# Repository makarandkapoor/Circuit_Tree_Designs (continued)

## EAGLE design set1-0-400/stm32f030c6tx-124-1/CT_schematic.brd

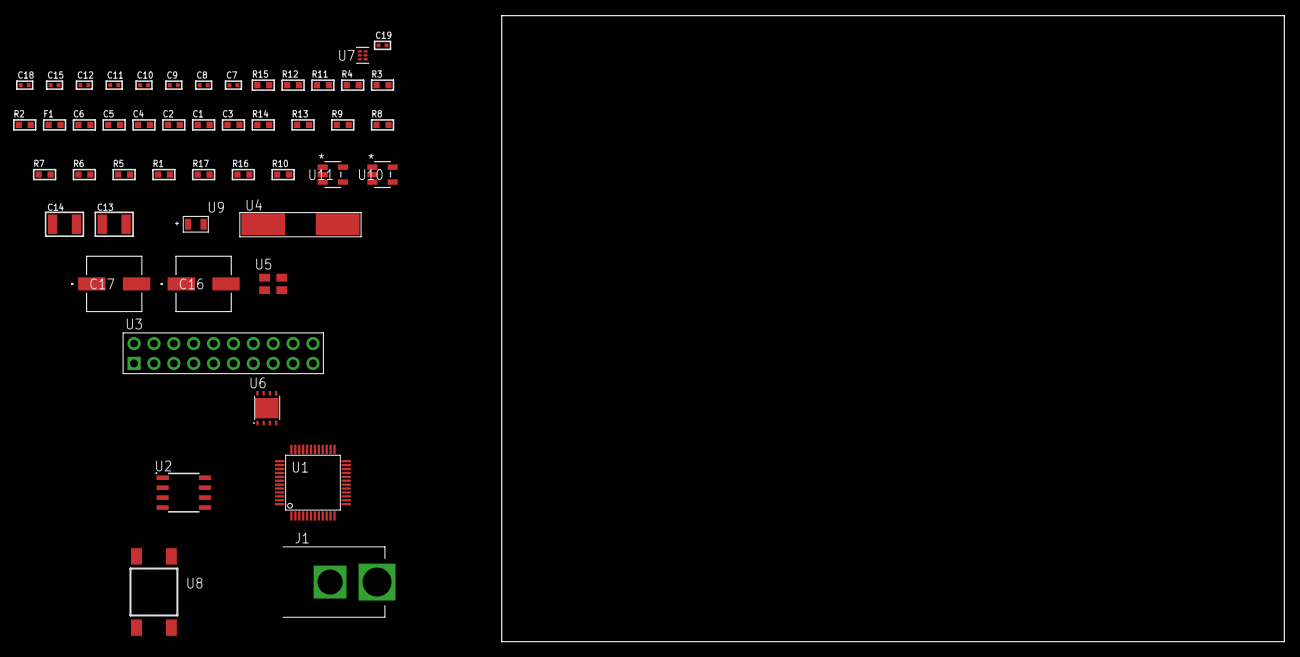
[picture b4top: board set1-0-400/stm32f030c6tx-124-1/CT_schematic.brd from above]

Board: 2 copper layers, 100.0 x 80.0 mm, 49 parts (0 on the bottom side), 27 nets, no tracks yet.

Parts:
C1, C2, C4: 1e-07; C0603
C3: 4.7e-06; C0603
C5: 1e-08; C0603
C6: 1e-06; C0603
C7, C8: 1e-11; C0402
C9, C11, C12, C18, C19: 1e-08; C0402
C10, C15: 1e-07; C0402
C13, C14: 1e-05; C1210
C16, C17: 0.0001; EXV-9H
F1: 240.0; L0603
J1: PJ-037B; PJ-037B_PACKAGE
R1, R5, R6, R7, R8, R9, R13, R14: 10000.0; R0603
R2, R12: 1000.0; R0603
R3: 1600.5; R0603
R4: 4700.0; R0603
R10: 100000.0; R0603
R11: 2231.0; R0603
R15: 9100.0; R0603
R16: 680000.0; R0603
R17: 120000.0; R0603
U1: STM32F030C6T6; LQFP48
U2: AT25040B-SSHL-T; SOIC-8
U3: TST-110-05-T-D-RA
U4: ABLS-25.000MHZ-B2F-T
U5: ASEK-32.768KHz-ECST; ASEK
U6: LP3878SDX-ADJ/NOPB; WSON-8
U7: TPS3895ADRYR; SON-6
U8: 4-1437565-2; SW_4-1437565-2
U9: Q65110A2395; LGM67K-G1J2-24-Z
U10, U11: nc7sz125m5x; NC7SZ125M5X

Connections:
CLK_CRYSTAL_U1_5: C7.1, U1.5, U4.1
CLK_CRYSTAL_U1_6: C8.1, U1.6, U4.2
CLK_U1_3: U1.3, U5.3
GND: C1.2, C2.2, C3.2, C4.2, C5.2, C6.2, C7.2, C8.2, C9.2, C10.2, C11.2, C12.2, C13.2, C14.2, C15.2, C16.2, C17.2, C18.2, C19.2, J1.2, R2.2, R5.2, R12.2, R15.2, R17.2, U1.8, U1.23, U1.47, U2.4, U3.4, U3.6, U3.8, U3.10, U3.12, U3.14, U3.16, U3.18, U3.20, U5.2, U6.3, U6.PAD, U7.2, U9.C, U10.2, U10.3, U11.1, U11.3
NET_U1_7: R4.1, U1.7, U11.4
NET_U1_9: C5.1, C6.1, F1.1, U1.9
NET_U1_44: R5.1, U1.44
NET_U1_45: R3.1, U1.45, U9.A
NET_U1_46: R1.1, U1.46, U8.3, U8.4
NET_U2_3: R6.1, U2.3
NET_U2_7: R8.1, U2.7
NET_U6_1: C12.1, U6.1
NET_U6_6: R11.2, R12.1, U6.6
NET_U6_8: R10.1, U6.8
NET_U7_1: R14.1, R15.1, U7.1
NET_U7_3: R16.2, R17.1, U7.3
NET_U7_4: R13.1, U7.4, U10.4, U11.2
NET_U8_1: R2.1, U8.1, U8.2
PROC_SPI1_MISO: U1.16, U2.2
PROC_SPI1_MOSI: U1.17, U2.5
PROC_SPI1_NSS: R7.1, U1.14, U2.1
PROC_SPI1_SCK: U1.15, U2.6
PROC_SYS_SWCLK: U1.37, U3.9
PROC_SYS_SWDIO: U1.34, U3.7
RST_OUT_U3_SRESET_B: R9.1, U3.15, U10.1
VCC_S1_14V1: C13.1, C16.1, C17.1, J1.1, R10.2, U6.4
VCC_TIER1_3V3: C1.1, C2.1, C3.1, C4.1, C9.1, C10.1, C11.1, C14.1, C15.1, C18.1, C19.1, F1.2, R1.2, R3.2, R4.2, R6.2, R7.2, R8.2, R9.2, R11.1, R13.2, R14.2, R16.1, U1.1, U1.24, U1.48, U2.8, U3.1, U5.4, U6.5, U7.6, U10.5, U11.5

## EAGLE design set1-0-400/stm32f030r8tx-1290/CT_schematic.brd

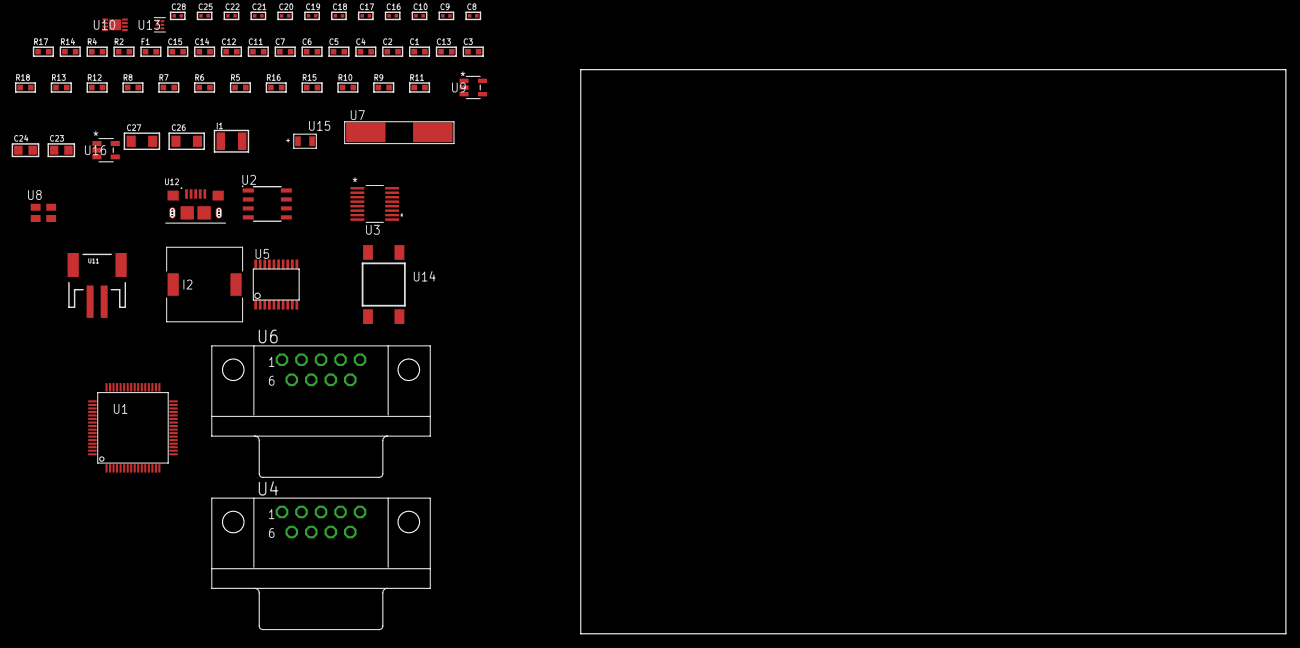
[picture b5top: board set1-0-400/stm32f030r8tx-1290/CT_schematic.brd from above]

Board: 2 copper layers, 63 parts (0 on the bottom side), 53 nets, no tracks yet.

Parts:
C1, C2, C4, C5: 1e-07; C0603
C3: 4.7e-06; C0603
C6: 1e-08; C0603
C7, C11, C12, C14, C15: 1e-06; C0603
C8, C9: 1e-11; C0402
C10, C22, C28: 1e-08; C0402
C13: 2.2e-07; C0603
C16, C17, C18, C19, C20, C21, C25: 1e-07; C0402
C23, C24: 1e-05; C0805
C26, C27: 1e-05; C1206
F1: 240.0; L0603
I1: 1e-05; L1210
I2: 2.5e-06; DR1040
R2: 1000.0; R0603
R4: 4700.0; R0603
R5, R6, R7, R8, R12, R13, R18: 10000.0; R0603
R9: 100000.0; R0603
R10: 220000.0; R0603
R11: 1000000.0; R0603
R14: 9100.0; R0603
R15: 680000.0; R0603
R16: 120000.0; R0603
R17: 2000.0; R0603
U1: STM32F030R8T6; LQFP64
U2: AT25640B-SSHL-T; SOIC-8
U3: LTC2804CGN-1#PBF; SSOP-16
U4, U6: 182-009-113R531; 182-009-MALE
U5: SP3203ECY-L/TR; TSSOP20-I
U7: ABLS-25.000MHZ-B2F-T
U8: ASEK-32.768KHz-ECST; ASEK
U9: ltc3406es5; TSOT-23-5
U10: MCP73831T-2ACI/MC; DFN8_2X3MC
U11: S2B-PH-SM4-TB(LF)(SN); JST-2-SMD
U12: 10118193-0001LF; FCI_10118193-0001LF
U13: TPS3895ADRYR; SON-6
U14: 4-1437565-2; SW_4-1437565-2
U15: Q65110A2395; LGM67K-G1J2-24-Z
U16: nc7sz125m5x; NC7SZ125M5X

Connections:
CLK_CRYSTAL_U1_5: C8.1, U1.5, U7.1
CLK_CRYSTAL_U1_6: C9.1, U1.6, U7.2
CLK_U1_3: U1.3, U8.3
GND: C1.2, C2.2, C3.2, C4.2, C5.2, C6.2, C7.2, C8.2, C9.2, C10.2, C11.2, C12.2, C14.2, C15.2, C16.2, C17.2, C20.2, C21.2, C22.2, C23.2, C24.1, C24.2, C25.2, C26.2, C27.2, C28.2, R2.2, R5.2, R10.2, R14.2, R16.2, R17.2, U1.12, U1.31, U1.63, U2.4, U3.8, U4.5, U5.18, U6.5, U8.2, U9.2, U10.6, U10.9, U11.2, U12.5, U12.6, U12.7, U12.8, U12.9, U13.2, U15.C, U16.1, U16.3
INPUT_USBPOWER_5V: C26.1, R18.2, U10.1, U10.2, U12.1
NET_U1_7: R4.1, U1.7, U16.4
NET_U1_13: C6.1, C7.1, F1.1, U1.13
NET_U1_60: R5.1, U1.60
NET_U1_62: U14.3, U14.4
NET_U2_3: R6.1, U2.3
NET_U2_7: R8.1, U2.7
NET_U3_6: C11.1, U3.6
NET_U3_7: C13.1, I1.2, U3.7
NET_U3_9: C12.1, U3.9
NET_U3_10: C13.2, U3.10
NET_U3_11: R9.1, U3.11
NET_U4_2: U3.1, U4.2
NET_U4_3: U3.3, U4.3
NET_U4_7: U3.2, U4.7
NET_U4_8: U3.4, U4.8
NET_U5_1: C18.1, U5.1
NET_U5_2: C20.1, U5.2
NET_U5_3: C18.2, U5.3
NET_U5_4: C19.1, U5.4
NET_U5_5: C19.2, U5.5
NET_U5_6: C21.1, U5.6
NET_U6_2: U5.14, U6.2
NET_U6_3: U5.17, U6.3
NET_U6_7: U5.13, U6.7
NET_U6_8: U5.16, U6.8
NET_U9_3: I2.1, U9.3
NET_U9_5: R10.1, R11.1, U9.5
NET_U9_ATNET_3: I2.2, R11.2
NET_U10_5: R18.1, U10.5
NET_U10_8: R17.1, U10.8
NET_U13_1: R13.1, R14.1, U13.1
NET_U13_3: R15.2, R16.1, U13.3
NET_U13_4: R12.1, U13.4, U16.2
NET_U14_1: R2.1, U14.1, U14.2
PROC_SPI1_MISO: U1.22, U2.2
PROC_SPI1_MOSI: U1.23, U2.5
PROC_SPI1_NSS: R7.1, U1.20, U2.1
PROC_SPI1_SCK: U1.21, U2.6
PROC_USART1_CTS: U1.44, U5.8
PROC_USART1_RTS: U1.45, U5.10
PROC_USART1_RX: U1.43, U5.11
PROC_USART1_TX: U1.42, U5.7
PROC_USART2_CTS: U1.14, U3.13
PROC_USART2_RTS: U1.15, U3.15
PROC_USART2_RX: U1.17, U3.16
PROC_USART2_TX: U1.16, U3.14
VCC_S1_3V7: C23.1, C27.1, U9.4, U10.3, U10.4, U11.1
VCC_TIER1_3V3: C1.1, C2.1, C3.1, C4.1, C5.1, C10.1, C14.1, C15.1, C16.1, C17.1, C22.1, C24.2, C25.1, C28.1, F1.2, I1.1, I2.2, R4.2, R6.2, R7.2, R8.2, R9.2, R11.2, R12.2, R13.2, R15.1, U1.1, U1.32, U1.64, U2.8, U3.5, U3.12, U5.12, U5.19, U8.4, U13.6, U16.5

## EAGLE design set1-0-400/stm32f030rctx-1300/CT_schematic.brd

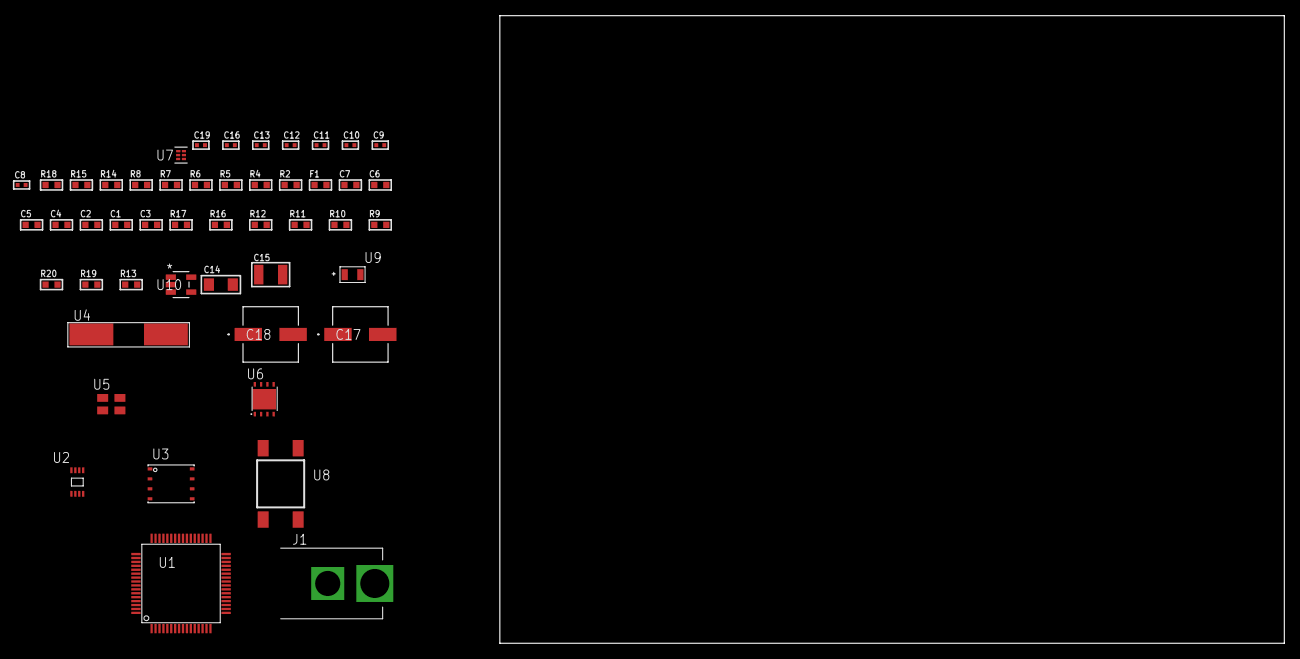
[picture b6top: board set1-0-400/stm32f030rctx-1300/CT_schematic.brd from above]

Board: 2 copper layers, 100.0 x 80.0 mm, 49 parts (0 on the bottom side), 24 nets, no tracks yet.

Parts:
C1, C2, C4, C5: 1e-07; C0603
C3: 4.7e-06; C0603
C6: 1e-08; C0603
C7: 1e-06; C0603
C8, C9: 1e-11; C0402
C10, C11, C12, C13, C19: 1e-08; C0402
C14: 1e-05; C1206
C15: 1e-05; C1210
C16: 1e-07; C0402
C17, C18: 0.0001; EXV-9H
F1: 240.0; L0603
J1: PJ-037B; PJ-037B_PACKAGE
R2, R15: 1000.0; R0603
R4: 4700.0; R0603
R5, R6, R7, R8: 2200.0; R0603
R9, R10, R11, R12, R16, R17: 10000.0; R0603
R13: 100000.0; R0603
R14: 2231.0; R0603
R18: 9100.0; R0603
R19: 680000.0; R0603
R20: 120000.0; R0603
U1: STM32F030RCT6; LQFP64
U2: 24AA04-I/MC; TDFN-8/6MM
U3: 24AA512-I/MF; DFN8-S
U4: ABLS-25.000MHZ-B2F-T
U5: ASEK-32.768KHz-ECST; ASEK
U6: LP3878SDX-ADJ/NOPB; WSON-8
U7: TPS3895ADRYR; SON-6
U8: 4-1437565-2; SW_4-1437565-2
U9: Q65110A2395; LGM67K-G1J2-24-Z
U10: nc7sz125m5x; NC7SZ125M5X

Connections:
CLK_CRYSTAL_U1_5: C8.1, U1.5, U4.1
CLK_CRYSTAL_U1_6: C9.1, U1.6, U4.2
CLK_U1_3: U1.3, U5.3
GND: C1.2, C2.2, C3.2, C4.2, C5.2, C6.2, C7.2, C8.2, C9.2, C10.2, C11.2, C12.2, C13.2, C14.2, C15.2, C16.2, C17.2, C18.2, C19.2, J1.2, R2.2, R9.2, R12.2, R15.2, R18.2, R20.2, U1.12, U1.18, U1.31, U1.47, U1.63, U2.4, U3.4, U5.2, U6.3, U6.PAD, U7.2, U9.C, U10.1, U10.3
NET_U1_7: R4.1, U1.7, U10.4
NET_U1_13: C6.1, C7.1, F1.1, U1.13
NET_U1_29: R7.1, U1.29, U2.6
NET_U1_30: R8.1, U1.30, U2.5
NET_U1_42: R5.1, U1.42, U3.6
NET_U1_43: R6.1, U1.43, U3.5
NET_U1_60: R9.1, U1.60
NET_U1_62: U8.3, U8.4
NET_U3_1: R10.1, U3.1
NET_U3_2: R11.1, U3.2
NET_U3_3: R12.1, U3.3
NET_U6_1: C13.1, U6.1
NET_U6_6: R14.2, R15.1, U6.6
NET_U6_8: R13.1, U6.8
NET_U7_1: R17.1, R18.1, U7.1
NET_U7_3: R19.2, R20.1, U7.3
NET_U7_4: R16.1, U7.4, U10.2
NET_U8_1: R2.1, U8.1, U8.2
VCC_S1_10V2: C14.1, C17.1, C18.1, J1.1, R13.2, U6.4
VCC_TIER1_3V3: C1.1, C2.1, C3.1, C4.1, C5.1, C10.1, C11.1, C12.1, C15.1, C16.1, C19.1, F1.2, R4.2, R5.2, R6.2, R7.2, R8.2, R10.2, R11.2, R14.1, R16.2, R17.2, R19.1, U1.1, U1.19, U1.32, U1.48, U1.64, U2.7, U2.8, U3.7, U3.8, U5.4, U6.5, U7.6, U10.5

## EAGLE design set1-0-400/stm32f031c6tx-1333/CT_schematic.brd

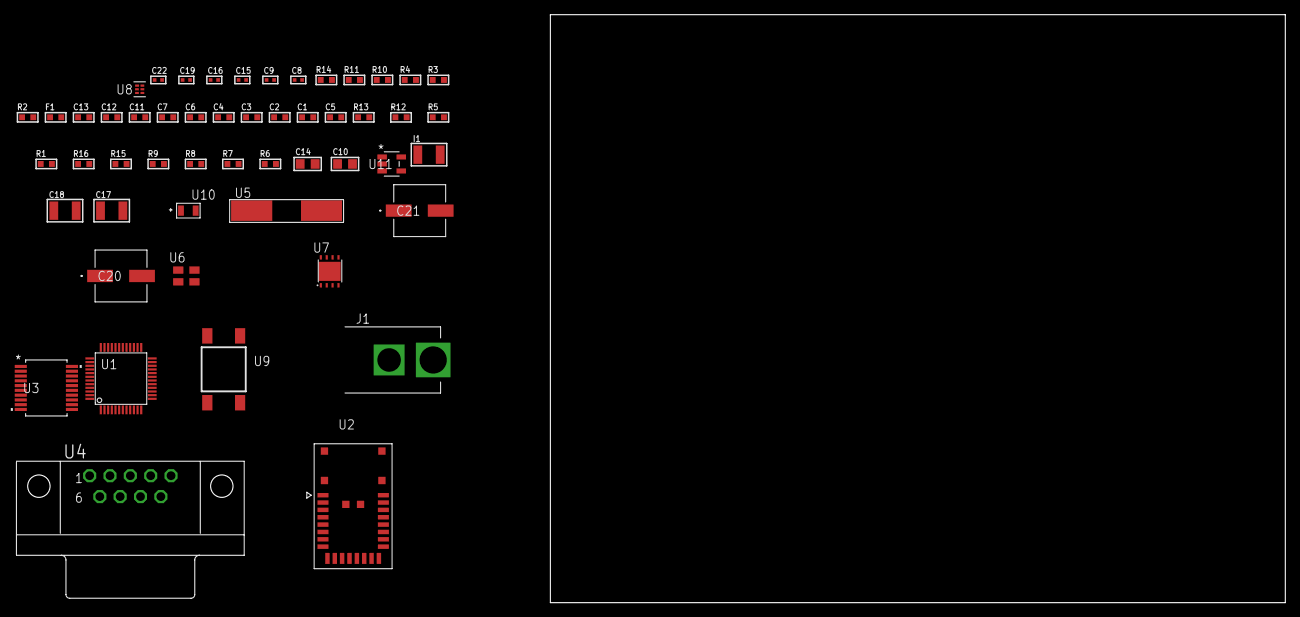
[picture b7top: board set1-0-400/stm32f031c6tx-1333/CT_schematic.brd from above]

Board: 2 copper layers, 100.0 x 80.0 mm, 52 parts (0 on the bottom side), 38 nets, no tracks yet.

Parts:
C1, C7, C11, C12, C13: 1e-06; C0603
C2, C3, C4: 1e-07; C0603
C5: 4.7e-06; C0603
C6: 1e-08; C0603
C8, C9: 1e-11; C0402
C10: 1e-05; C0805
C14: 4.7e-06; C0805
C15, C16, C22: 1e-08; C0402
C17, C18: 1e-05; C1210
C19: 1e-07; C0402
C20, C21: 0.0001; EXV-9H
F1: 240.0; L0603
I1: 1.5e-05; L1210
J1: PJ-037B; PJ-037B_PACKAGE
R1, R5, R12, R13: 10000.0; R0603
R2, R11: 1000.0; R0603
R3: 1600.5; R0603
R4: 4700.0; R0603
R6, R7, R8, R9: 100000.0; R0603
R10: 2231.0; R0603
R14: 9100.0; R0603
R15: 680000.0; R0603
R16: 120000.0; R0603
U1: stm32f031c6t6; LQFP48
U2: A2500R24A00GM
U3: MAX3218EAP+T; SSOP-20
U4: 182-009-113R531; 182-009-MALE
U5: ABLS-25.000MHZ-B2F-T
U6: ASEK-32.768KHz-ECST; ASEK
U7: LP3878SDX-ADJ/NOPB; WSON-8
U8: TPS3895ADRYR; SON-6
U9: 4-1437565-2; SW_4-1437565-2
U10: Q65110A2395; LGM67K-G1J2-24-Z
U11: nc7sz125m5x; NC7SZ125M5X

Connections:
CLK_CRYSTAL_U1_5: C8.1, U1.5, U5.1
CLK_CRYSTAL_U1_6: C9.1, U1.6, U5.2
CLK_U1_3: U1.3, U6.3
GND: C1.2, C2.2, C3.2, C4.2, C5.2, C6.2, C7.2, C8.2, C9.2, C10.2, C11.2, C12.2, C13.2, C15.2, C16.2, C17.2, C18.2, C19.2, C20.2, C21.2, C22.2, J1.2, R2.2, R5.2, R11.2, R14.2, R16.2, U1.8, U1.23, U1.47, U2.8, U2.17, U3.5, U3.17, U3.20, U4.5, U6.2, U7.3, U7.PAD, U8.2, U10.C, U11.1, U11.3
NET_U1_7: R4.1, U1.7, U11.4
NET_U1_9: C6.1, C7.1, F1.1, U1.9
NET_U1_44: R5.1, U1.44
NET_U1_45: R3.1, U1.45, U10.A
NET_U1_46: R1.1, U1.46, U9.3, U9.4
NET_U3_1: I1.1, U3.1
NET_U3_2: R6.1, U3.2
NET_U3_3: R7.1, U3.3
NET_U3_4: R8.1, U3.4
NET_U3_15: C13.1, U3.15
NET_U3_16: C14.2, U3.16
NET_U3_18: C14.1, U3.18
NET_U3_19: C12.1, U3.19
NET_U4_2: U3.12, U4.2
NET_U4_3: U3.14, U4.3
NET_U4_7: U3.11, U4.7
NET_U4_8: U3.13, U4.8
NET_U7_1: C16.1, U7.1
NET_U7_6: R10.2, R11.1, U7.6
NET_U7_8: R9.1, U7.8
NET_U8_1: R13.1, R14.1, U8.1
NET_U8_3: R15.2, R16.1, U8.3
NET_U8_4: R12.1, U8.4, U11.2
NET_U9_1: R2.1, U9.1, U9.2
PROC_SPI1_MISO: U1.16, U2.10
PROC_SPI1_MOSI: U1.17, U2.11
PROC_SPI1_NSS: U1.14, U2.12
PROC_SPI1_SCK: U1.15, U2.9
PROC_USART1_CTS: U1.10, U3.8
PROC_USART1_RTS: U1.11, U3.10
PROC_USART1_RX: U1.13, U3.9
PROC_USART1_TX: U1.12, U3.7
VCC_S1_13V5: C17.1, C20.1, C21.1, J1.1, R9.2, U7.4
VCC_TIER1_3V3: C1.1, C2.1, C3.1, C4.1, C5.1, C10.1, C11.1, C15.1, C18.1, C19.1, C22.1, F1.2, I1.2, R1.2, R3.2, R4.2, R6.2, R7.2, R8.2, R10.1, R12.2, R13.2, R15.1, U1.1, U1.24, U1.48, U2.18, U3.6, U6.4, U7.5, U8.6, U11.5

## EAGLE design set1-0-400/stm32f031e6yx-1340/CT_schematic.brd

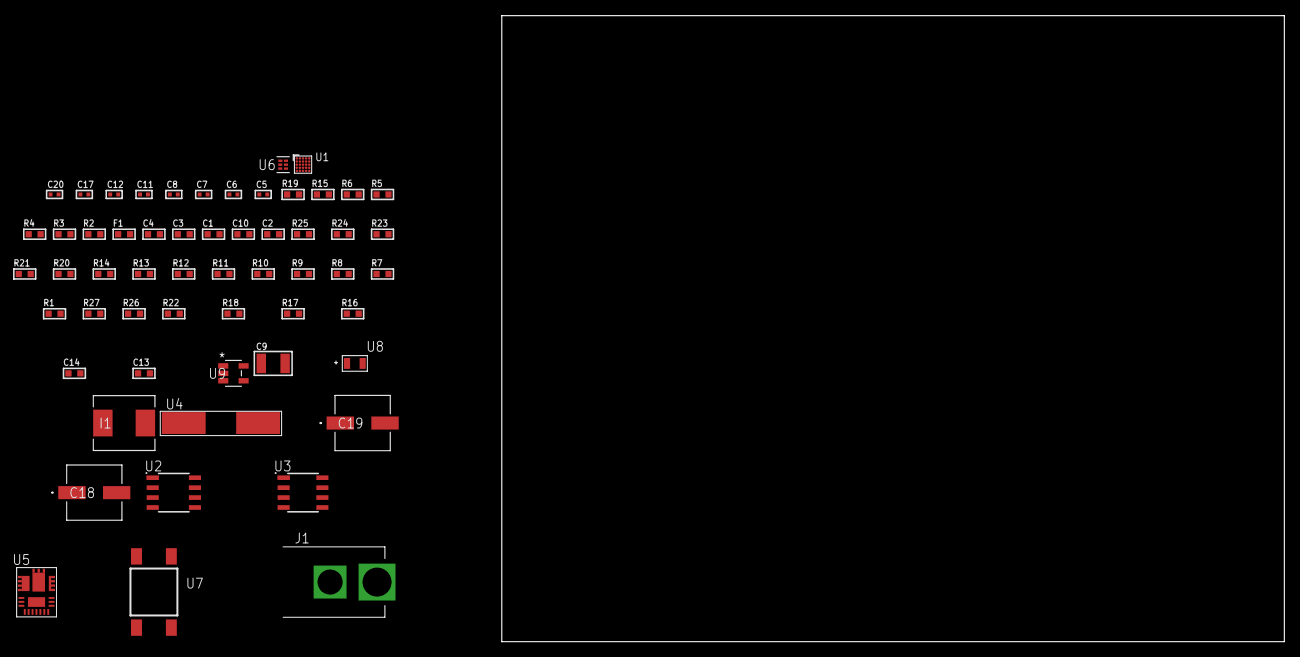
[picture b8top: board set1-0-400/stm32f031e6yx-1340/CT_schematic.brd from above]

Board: 2 copper layers, 100.0 x 80.0 mm, 57 parts (0 on the bottom side), 36 nets, no tracks yet.

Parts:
C1: 1e-07; C0603
C2: 4.7e-06; C0603
C3: 1e-08; C0603
C4: 1e-06; C0603
C5, C6: 1e-11; C0402
C7, C8, C20: 1e-08; C0402
C9: 0.0001; C1210
C10: 2.2e-06; C0603
C11, C12, C17: 1e-07; C0402
C13: 8.5935703950126e-09; R0603
C14: 2.929626271027e-07; R0603
C18, C19: 0.0001; EXV-9H
F1: 240.0; L0603
I1: 6.8e-07; IND25X25CZ
J1: PJ-037B; PJ-037B_PACKAGE
R1, R7, R8, R9, R10, R11, R12, R13, R14, R23, R24: 10000.0; R0603
R2: 1000.0; R0603
R3: 1270.0; R0603
R4: 4700.0; R0603
R5, R6: 2200.0; R0603
R15: 0.1; R0603
R16: 4030.2416170974; R0603
R17: 1007.5604042744; R0603
R18: 59.319518072289; R0603
R19: 130.0; R0603
R20: 39000.0; R0603
R21: 49900.0; R0603
R22: 5216.2133333333; R0603
R25: 18000.0; R0603
R26: 470000.0; R0603
R27: 120000.0; R0603
U1: stm32f031e6y7; WLCSP25
U2: AT25040B-SSHL-T; SOIC-8
U3: AT24C02D-SSHM-T; AT24C02D
U4: ABLS-25.000MHZ-B2F-T
U5: IR3899MTR1PBF
U6: TPS3895ADRYR; SON-6
U7: 4-1437565-2; SW_4-1437565-2
U8: Q65110A2395; LGM67K-G1J2-24-Z
U9: nc7sz125m5x; NC7SZ125M5X

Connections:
CLK_CRYSTAL_U1_A5: C5.1, U1.A5, U4.1
CLK_CRYSTAL_U1_B5: C6.1, U1.B5, U4.2
GND: C1.2, C2.2, C3.2, C4.2, C5.2, C6.2, C7.2, C8.2, C10.2, C11.2, C12.2, C17.2, C18.2, C19.2, C20.2, J1.2, R2.2, R7.2, R11.2, R13.2, R14.2, R15.1, R15.2, R17.2, R20.2, R22.2, R25.2, R27.2, U1.E1, U2.4, U3.4, U5.4, U5.11, U5.17, U6.2, U8.C, U9.1, U9.3
NET_U1_A3: R6.1, U1.A3, U3.5
NET_U1_A4: R7.1, U1.A4
NET_U1_B2: R5.1, U1.B2, U3.6
NET_U1_C5: R4.1, U1.C5, U9.4
NET_U1_D5: C3.1, C4.1, F1.1, U1.D5
NET_U1_E4: R3.1, U1.E4, U8.A
NET_U1_E5: R1.1, U1.E5, U7.3, U7.4
NET_U2_3: R8.1, U2.3
NET_U2_7: R10.1, U2.7
NET_U3_1: R12.1, U3.1
NET_U3_2: R13.1, U3.2
NET_U3_3: R14.1, U3.3
NET_U3_7: R11.1, U3.7
NET_U5_1: C13.1, R16.1, R17.1, R18.1, R19.1, U5.1, U5.8
NET_U5_2: C12.1, U5.2
NET_U5_3: C13.2, C14.1, C14.2, U5.3
NET_U5_5: R20.1, U5.5
NET_U5_10: C10.1, U5.10
NET_U5_12: C9.1, I1.1, U5.12
NET_U5_14: C9.2, U5.14
NET_U5_15: R21.1, R22.1, U5.15
NET_U5_ATNET_3: I1.2, R16.2
NET_U5_ATNET_4: C14.2, R18.2
NET_U6_1: R24.1, R25.1, U6.1
NET_U6_3: R26.2, R27.1, U6.3
NET_U6_4: R23.1, U6.4, U9.2
NET_U7_1: R2.1, U7.1, U7.2
PROC_SPI1_MISO: U1.D3, U2.2
PROC_SPI1_MOSI: U1.C2, U2.5
PROC_SPI1_NSS: R9.1, U1.B3, U2.1
PROC_SPI1_SCK: U1.C3, U2.6
VCC_S1_16V6: C11.1, C18.1, C19.1, J1.1, R21.2, U5.9
VCC_TIER1_2V5: C1.1, C2.1, C7.1, C8.1, C17.1, C20.1, F1.2, I1.2, R1.2, R3.2, R4.2, R5.2, R6.2, R8.2, R9.2, R10.2, R12.2, R16.2, R23.2, R24.2, R26.1, U1.D1, U2.8, U3.8, U6.6, U9.5
